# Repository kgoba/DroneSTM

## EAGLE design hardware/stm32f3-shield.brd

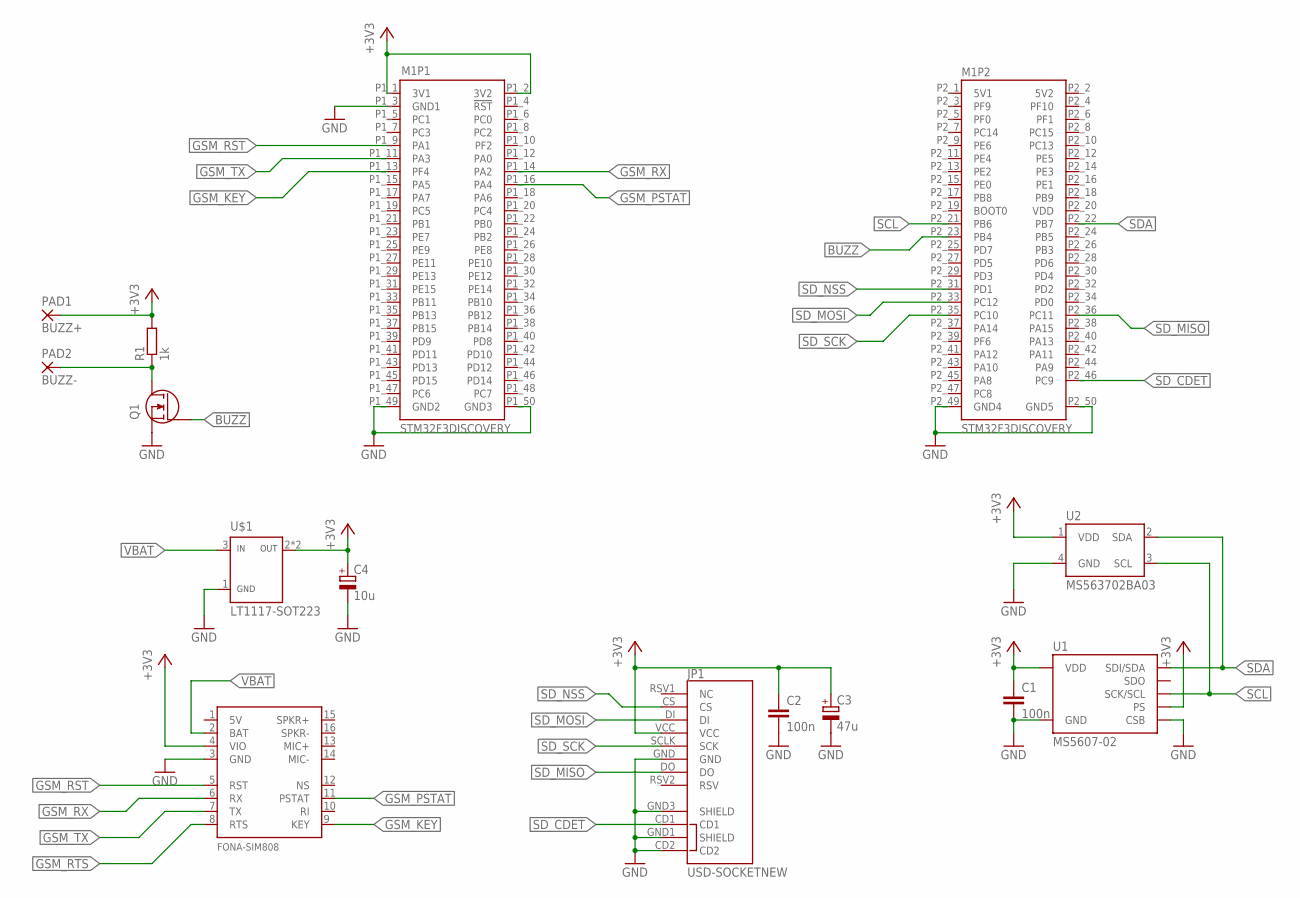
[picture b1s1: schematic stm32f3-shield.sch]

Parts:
C1, C2: 100n; C0805K
C3: 47u; SMC_B
C4: 10u; SMC_B
JP1: USD-SOCKETNEW; MICRO-SD-SOCKET-PP
M1: STM32F3DISCOVERY
M2: FONA-SIM808
PAD1: BUZZ+; 2,54/0,8
PAD2: BUZZ-; 2,54/0,8
Q1: MOSFET-N-SOT23-3; SOT23-3
R1: 1k; R0603
U1: MS5607-02; LGA8
U2: MS563702BA03; MS5637
U$1: LT1117-SOT223; SOT223

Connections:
+3V3: C1.1, C2.1, C3.+, C4.+, JP1.VCC, M1.P1_1 (3V1), M1.P1_2 (3V2), M2.4 (VIO), PAD1.1, R1.2, U1.1 (VDD), U1.2 (PS), U2.1 (VDD), U$1.2 (OUT), U$1.4 (OUT)
BUZZ: M1.P2_23 (PB4), Q1.1 (G)
GND: C1.2, C2.2, C3.-, C4.-, JP1.CD2, JP1.GND, JP1.GND1 (SHIELD), JP1.GND3 (SHIELD), M1.P1_3 (GND1), M1.P1_49 (GND2), M1.P1_50 (GND3), M1.P2_49 (GND4), M1.P2_50 (GND5), M2.3 (GND), Q1.2 (S), U1.3 (GND), U1.4 (CSB), U1.5 (CSB), U2.4 (GND), U$1.1 (GND)
GSM_KEY: M1.P1_13 (PF4), M2.9 (KEY)
GSM_PSTAT: M1.P1_16 (PA4), M2.11 (PSTAT)
GSM_RST: M1.P1_9 (PA1), M2.5 (RST)
GSM_RTS: M2.8 (RTS)
GSM_RX: M1.P1_14 (PA2), M2.6 (RX)
GSM_TX: M1.P1_11 (PA3), M2.7 (TX)
unnamed: PAD2.1, Q1.3 (D), R1.1
SCL: M1.P2_21 (PB6), U1.8 (SCK/SCL), U2.3 (SCL)
SDA: M1.P2_22 (PB7), U1.7 (SDI/SDA), U2.2 (SDA)
SD_CDET: JP1.CD1, M1.P2_46 (PC9)
SD_MISO: JP1.DO, M1.P2_36 (PC11)
SD_MOSI: JP1.DI, M1.P2_33 (PC12)
SD_NSS: JP1.CS, M1.P2_31 (PD1)
SD_SCK: JP1.SCLK (SCK), M1.P2_35 (PC10)
VBAT: M2.2 (BAT), U$1.3 (IN)

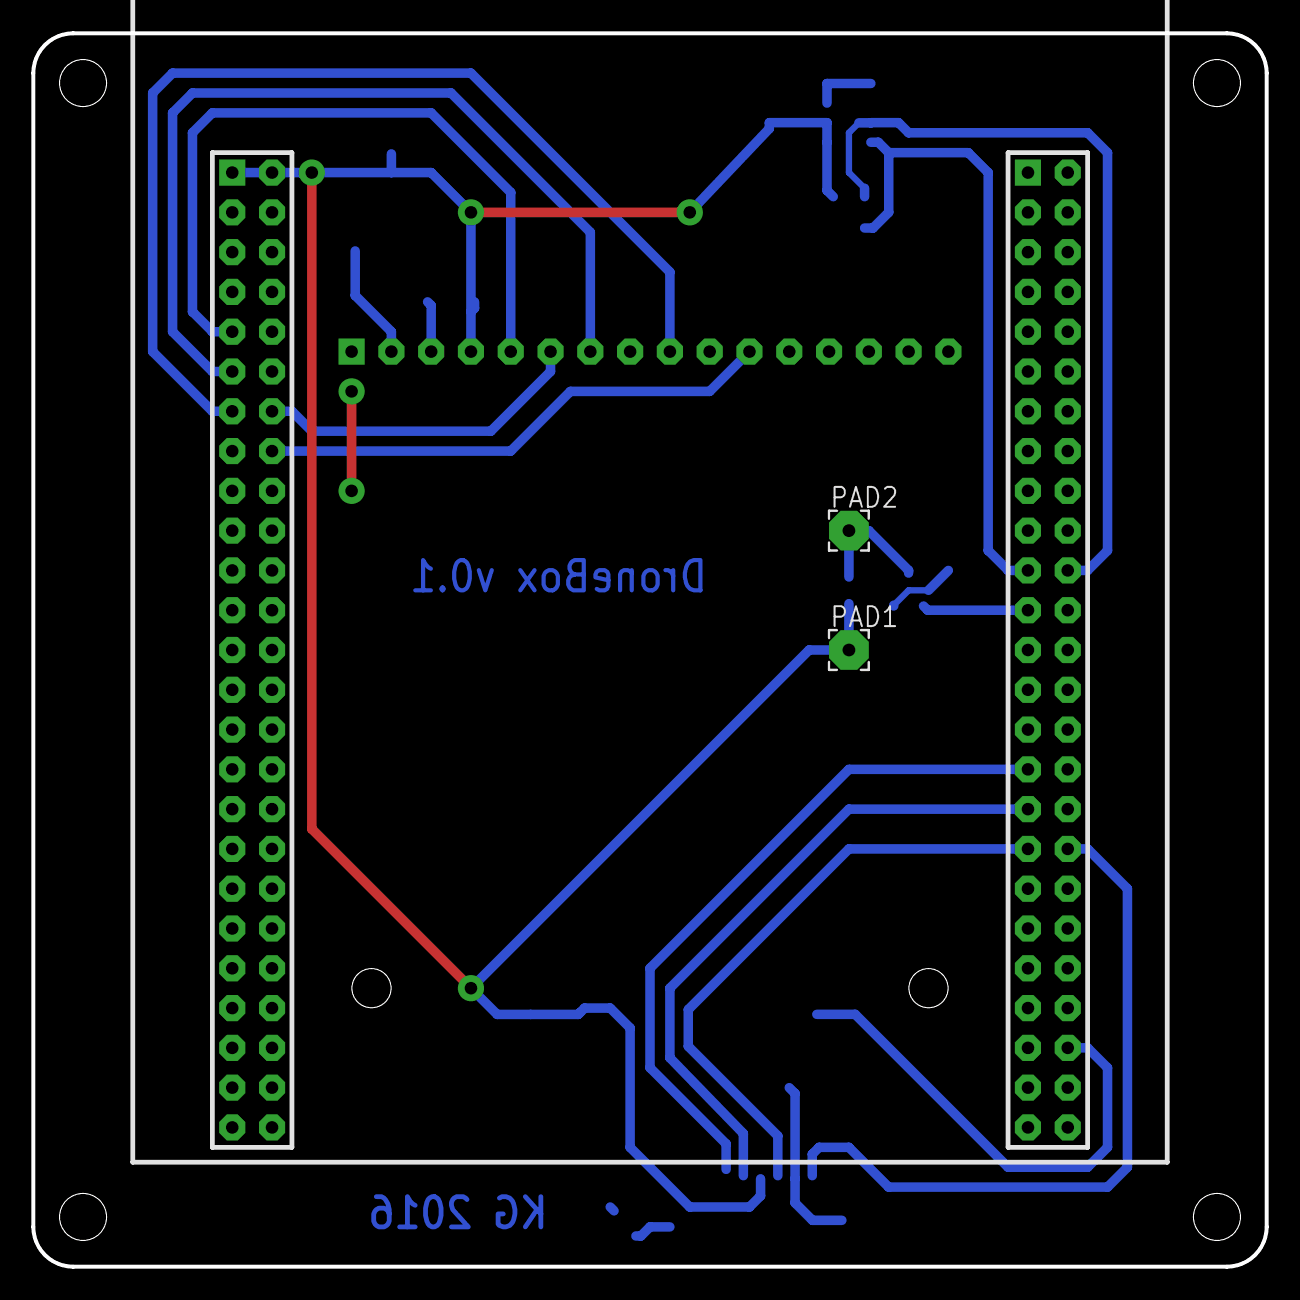
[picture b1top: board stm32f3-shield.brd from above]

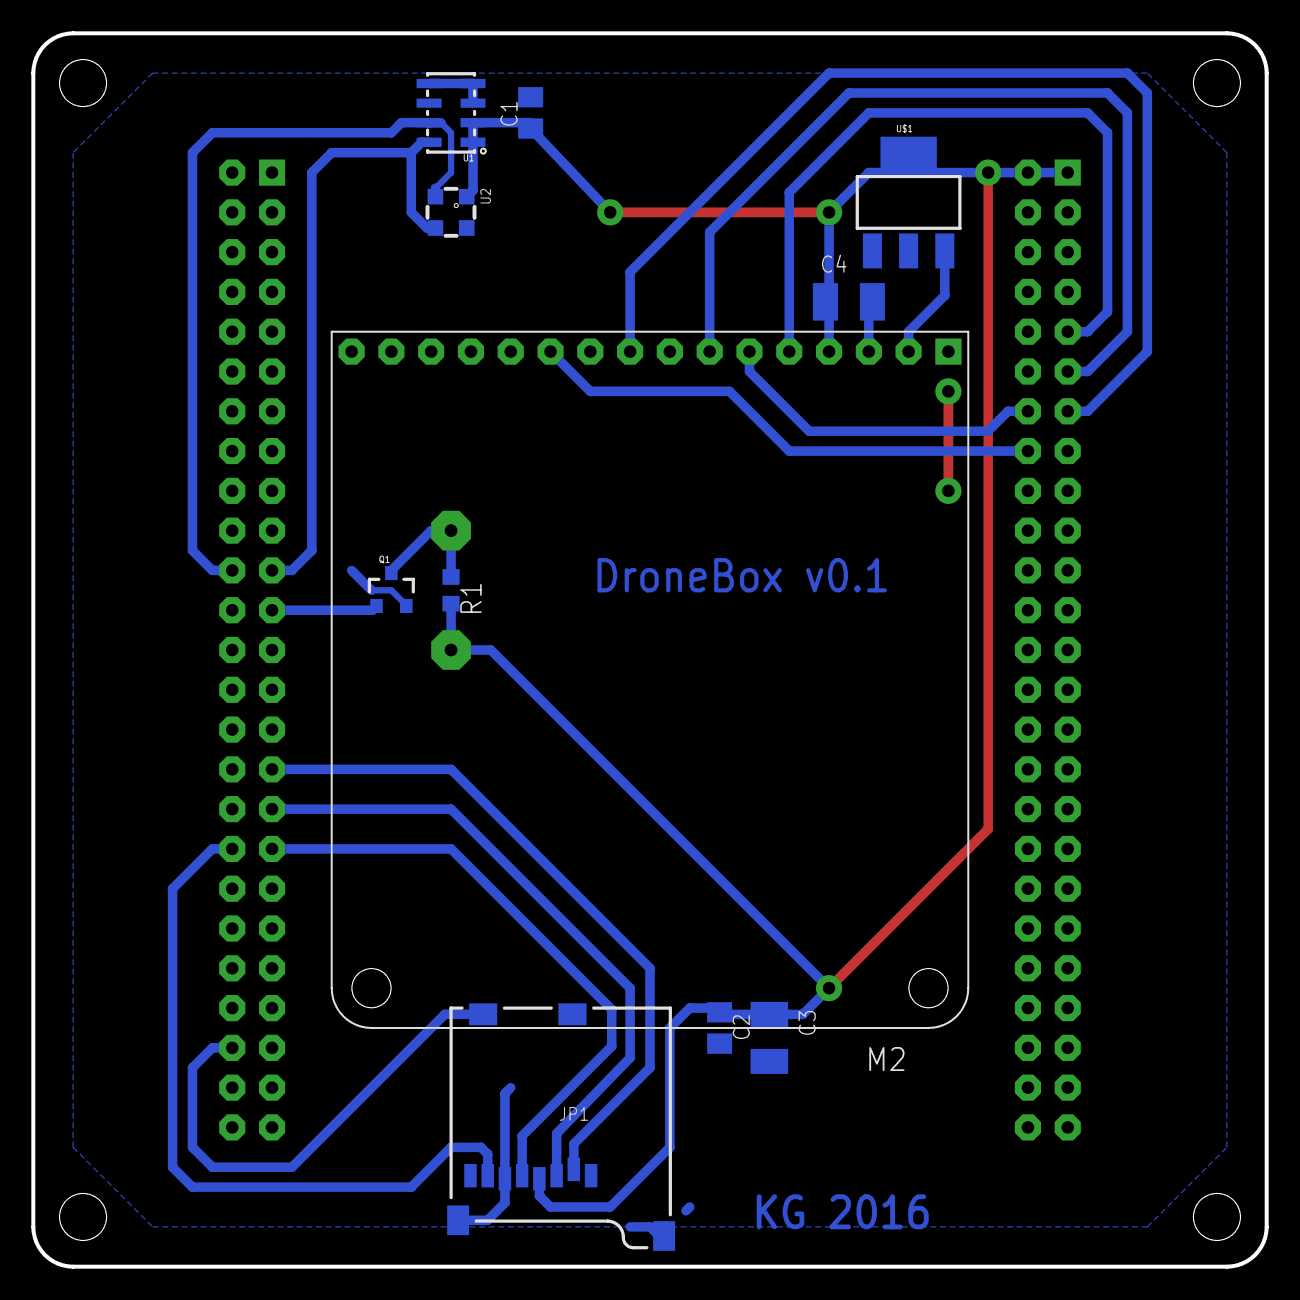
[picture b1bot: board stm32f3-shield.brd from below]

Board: 2 copper layers, 78.7 x 78.7 mm, 14 parts (11 on the bottom side), 17 nets.

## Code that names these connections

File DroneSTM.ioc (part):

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Mcu.Name=STM32F303V(B-C)Tx
Mcu.Package=LQFP100
Mcu.UserName=STM32F303VCTx
PA0.GPIOParameters=GPIO_Label
PA0.GPIO_Label=B1 [Blue PushButton]
PA0.Signal=GPIO_Input
PA1.GPIOParameters=GPIO_Label,GPIO_ModeDefaultOutputPP,PinState
PA1.GPIO_Label=GSM_RST
PA1.GPIO_ModeDefaultOutputPP=GPIO_MODE_OUTPUT_OD
PA1.PinState=GPIO_PIN_SET
PA1.Signal=GPIO_Output
PA11.GPIOParameters=GPIO_Label
PA11.GPIO_Label=DM
PA11.Mode=Device
PA11.Signal=USB_DM
PA12.GPIOParameters=GPIO_Label
PA12.GPIO_Label=DP
PA12.Mode=Device
PA12.Signal=USB_DP
PA13.GPIOParameters=GPIO_Label
PA13.GPIO_Label=SWDIO
PA13.Mode=Serial_Wire
PA13.Signal=SYS_JTMS-SWDIO
PA14.GPIOParameters=GPIO_Label
PA14.GPIO_Label=SWCLK
PA14.Mode=Serial_Wire
PA14.Signal=SYS_JTCK-SWCLK
PA2.GPIOParameters=GPIO_Label
PA2.GPIO_Label=GSM_RX
PA2.Mode=Asynchronous
PA2.Signal=USART2_TX
PA3.GPIOParameters=GPIO_Label
PA3.GPIO_Label=GSM_TX
PA3.Mode=Asynchronous
PA3.Signal=USART2_RX
PA4.GPIOParameters=GPIO_Label
PA4.GPIO_Label=GSM_PSTAT
PA4.Signal=GPIO_Input
PA5.GPIOParameters=GPIO_Label
PA5.GPIO_Label=SPI1_SCK [L3GD20_SCL/SPC]
PA5.Mode=Full_Duplex_Master
PA5.Signal=SPI1_SCK
PA6.GPIOParameters=GPIO_Label
PA6.GPIO_Label=SPI1_MISO [L3GD20_SA0/SDO]
PA6.Mode=Full_Duplex_Master
PA6.Signal=SPI1_MISO
PA7.GPIOParameters=GPIO_Label
PA7.GPIO_Label=SPI1_MISO [L3GD20_SDA/SDI/SDO]
PA7.Mode=Full_Duplex_Master
PA7.Signal=SPI1_MOSI
PB3.GPIOParameters=GPIO_Label
PB3.GPIO_Label=SWO
PB3.Signal=SYS_JTDO-TRACESWO
PB4.GPIOParameters=GPIO_Label
PB4.GPIO_Label=BUZZER
PB4.Signal=S_TIM3_CH1
PB6.GPIOParameters=GPIO_Label
PB6.GPIO_Label=I2C1_SCL [LSM303DLHC_SCL]
PB6.Mode=I2C
PB6.Signal=I2C1_SCL
PB7.GPIOParameters=GPIO_Label
PB7.GPIO_Label=I2C1_SDA [LSM303DLHC_SDA]
PB7.Mode=I2C
PB7.Signal=I2C1_SDA
PC10.GPIOParameters=GPIO_Label
PC10.GPIO_Label=SD_SCK
PC10.Mode=Full_Duplex_Master
PC10.Signal=SPI3_SCK
PC11.GPIOParameters=GPIO_Label,GPIO_PuPd
PC11.GPIO_Label=SD_MISO
PC11.GPIO_PuPd=GPIO_PULLUP
PC11.Mode=Full_Duplex_Master
PC11.Signal=SPI3_MISO
PC12.GPIOParameters=GPIO_Label
PC12.GPIO_Label=SD_MOSI
PC12.Mode=Full_Duplex_Master
PC12.Signal=SPI3_MOSI
PC14-OSC32_IN.Mode=LSE-External-Oscillator
PC14-OSC32_IN.Signal=RCC_OSC32_IN
PC15-OSC32_OUT.GPIOParameters=GPIO_Label
PC15-OSC32_OUT.GPIO_Label=OSC32_OUT
PC15-OSC32_OUT.Mode=LSE-External-Oscillator
PC15-OSC32_OUT.Signal=RCC_OSC32_OUT
PC9.GPIOParameters=GPIO_Label,GPIO_PuPd
PC9.GPIO_Label=SD_CDET
PC9.GPIO_PuPd=GPIO_PULLUP
PC9.Signal=GPIO_Input
PD1.GPIOParameters=GPIO_Label
PD1.GPIO_Label=SD_NSS
PD1.Signal=GPIO_Output
PD3.Mode=CTS_Only
PD3.Signal=USART2_CTS
PE0.GPIOParameters=GPIO_Label,GPIO_ModeDefaultEXTI
PE0.GPIO_Label=MEMS_INT1 [L3GD20_INT1]
PE0.GPIO_ModeDefaultEXTI=GPIO_MODE_EVT_RISING
PE0.Signal=GPXTI0
PE1.GPIOParameters=GPIO_Label,GPIO_ModeDefaultEXTI
PE1.GPIO_Label=MEMS_INT2 [L3GD20_DRDY/INT2]
PE1.GPIO_ModeDefaultEXTI=GPIO_MODE_EVT_RISING
PE1.Signal=GPXTI1
PE10.GPIOParameters=GPIO_Label
PE10.GPIO_Label=LD5 [Orange Led]
PE10.Signal=GPIO_Output
PE11.GPIOParameters=GPIO_Label
PE11.GPIO_Label=LD7 [Green Led]
PE11.Signal=GPIO_Output
PE12.GPIOParameters=GPIO_Label
PE12.GPIO_Label=LD9 [Blue Led]
PE12.Signal=GPIO_Output
PE13.GPIOParameters=GPIO_Label
PE13.GPIO_Label=LD10 [Red Led]
PE13.Signal=GPIO_Output
PE14.GPIOParameters=GPIO_Label
PE14.GPIO_Label=LD8 [Orange Led]
PE14.Signal=GPIO_Output
PE15.GPIOParameters=GPIO_Label
PE15.GPIO_Label=LD6 [Green Led]
PE15.Signal=GPIO_Output
PE2.GPIOParameters=GPIO_Label,GPIO_ModeDefaultEXTI
PE2.GPIO_Label=DRDY [LSM303DLHC_DRDY]
PE2.GPIO_ModeDefaultEXTI=GPIO_MODE_EVT_RISING
PE2.Signal=GPXTI2
PE3.GPIOParameters=GPIO_Label
PE3.GPIO_Label=CS_I2C/SPI [L3GD20_CS_I2C/SPI]
PE3.Signal=GPIO_Output
PE4.GPIOParameters=GPIO_Label,GPIO_ModeDefaultEXTI
PE4.GPIO_Label=MEMS_INT3 [LSM303DLHC_INT1]
PE4.GPIO_ModeDefaultEXTI=GPIO_MODE_EVT_RISING
PE4.Signal=GPXTI4
PE5.GPIOParameters=GPIO_Label,GPIO_ModeDefaultEXTI
PE5.GPIO_Label=MEMS_INT4 [LSM303DLHC_INT2]
PE5.GPIO_ModeDefaultEXTI=GPIO_MODE_EVT_RISING
PE5.Signal=GPXTI5
PE8.GPIOParameters=GPIO_Label
PE8.GPIO_Label=LD4 [Blue Led]
PE8.Signal=GPIO_Output
PE9.GPIOParameters=GPIO_Label
PE9.GPIO_Label=LD3 [Red Led]
PE9.Signal=GPIO_Output
PF0-OSC_IN.GPIOParameters=GPIO_Label
PF0-OSC_IN.GPIO_Label=OSC_IN
PF0-OSC_IN.Mode=HSE-External-Oscillator
PF0-OSC_IN.Signal=RCC_OSC_IN
PF1-OSC_OUT.Mode=HSE-External-Oscillator
PF1-OSC_OUT.Signal=RCC_OSC_OUT
PF4.GPIOParameters=GPIO_Label,GPIO_PuPd
PF4.GPIO_Label=GSM_KEY
PF4.GPIO_PuPd=GPIO_NOPULL
PF4.Signal=GPIO_Input
RCC.HSEPLLFreq_Value=8000000
RCC.HSE_VALUE=8000000
RCC.SYSCLKFreq_VALUE=72000000
RCC.SYSCLKSourceVirtual=RCC_SYSCLKSOURCE_PLLCLK
board=STM32F3DISCOVERY
boardIOC=true

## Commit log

2016-06-21 Working makefile
2016-06-21 Added map and lst files
2016-06-21 STM32CubeMX project
2016-06-21 LED blinking task
2016-06-21 Moved include to user section
2016-06-21 Added second task
2016-06-23 USB CDC test code
2016-06-25 Updated SD/MMC driver
2016-06-25 Isolated USART interrupt
2016-07-11 Added CubeMX sources
2016-07-11 Added mbed sources
2016-07-11 Added barometer and vario
2016-07-11 Added debug UART
2016-07-12 Updated to newer mbed version
2016-07-12 Updated to newer mbed, fixed multitasking
2016-07-12 Two threads
2016-07-12 Removed garbage
2016-07-12 mbed build instructions
2016-07-12 Fixed flash target
2016-07-12 Added NMEA/TK102 processing
2016-07-13 Switched to TCP/IP implementation
2016-07-14 Include FatFs source
2016-07-14 Desperate updates
2016-07-16 Added Cube generated sources
2016-07-16 Checksum calculation
2016-07-16 Minor update
2016-07-26 Fixed TK102 date issue
2016-11-02 Added schematics and FONA module on/off
2016-11-05 Added SD card reading
2016-11-05 Final fixes

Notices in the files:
parts and their libraries:
SparkFun-Connectors: Licensing: Creative Commons ShareAlike 4.0 International - https://creativecommons.org/licenses/by-sa/4.0
